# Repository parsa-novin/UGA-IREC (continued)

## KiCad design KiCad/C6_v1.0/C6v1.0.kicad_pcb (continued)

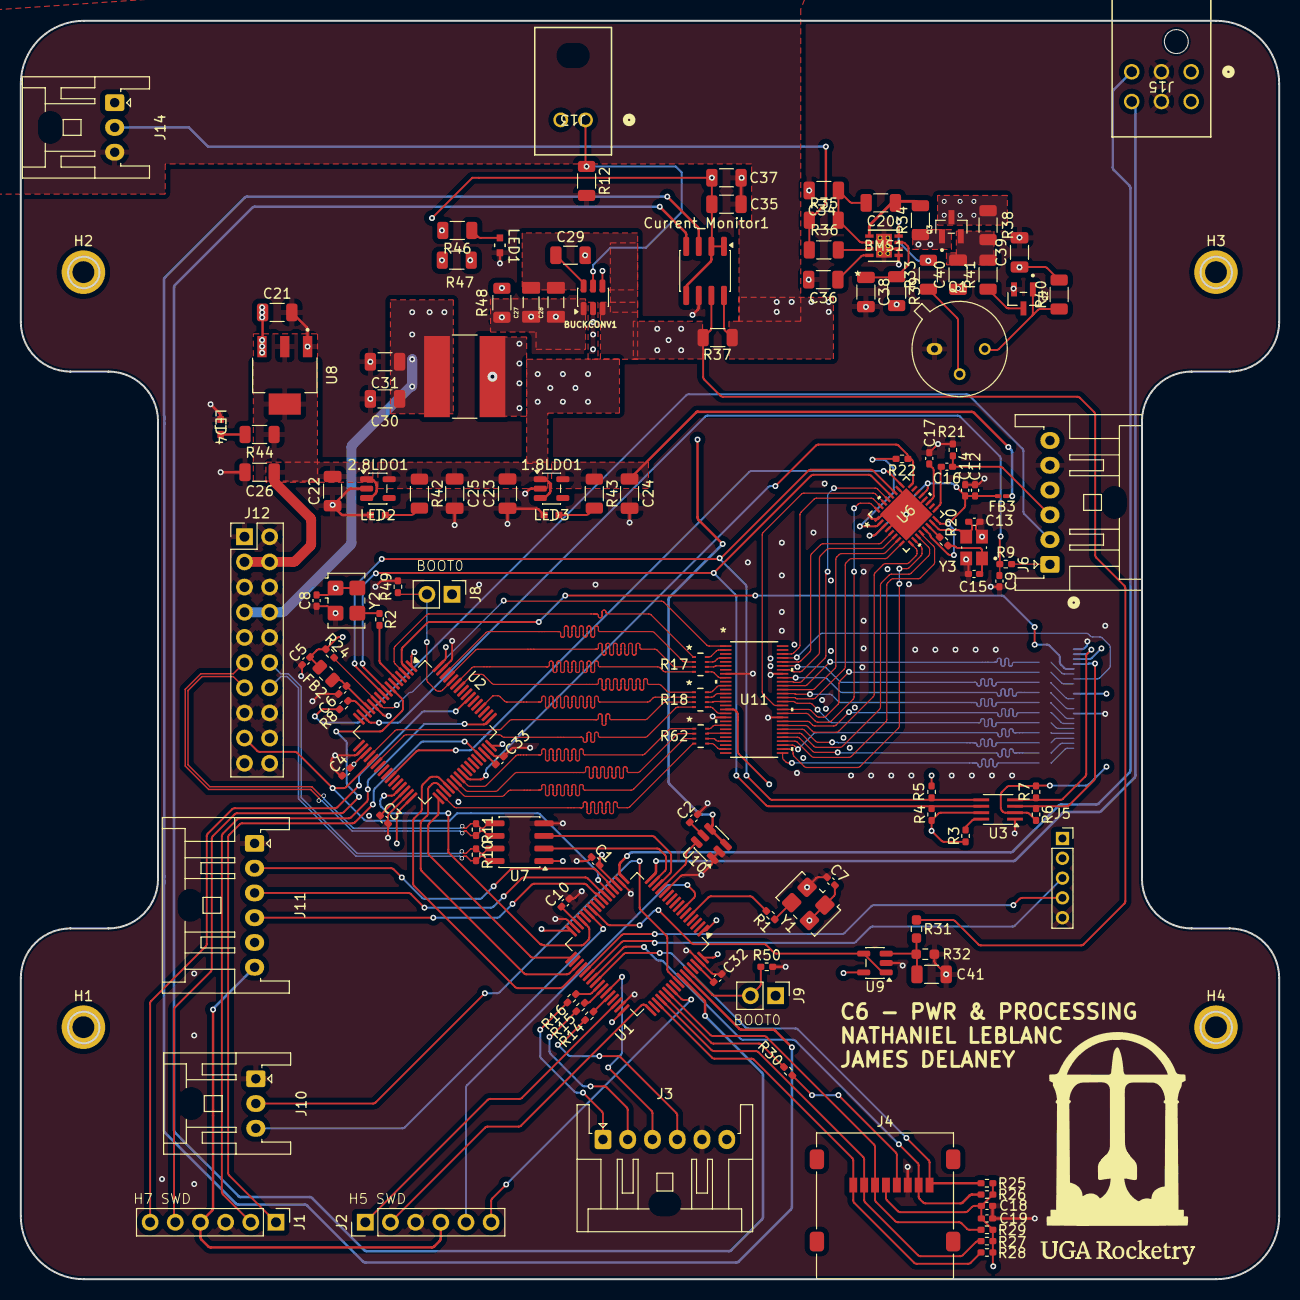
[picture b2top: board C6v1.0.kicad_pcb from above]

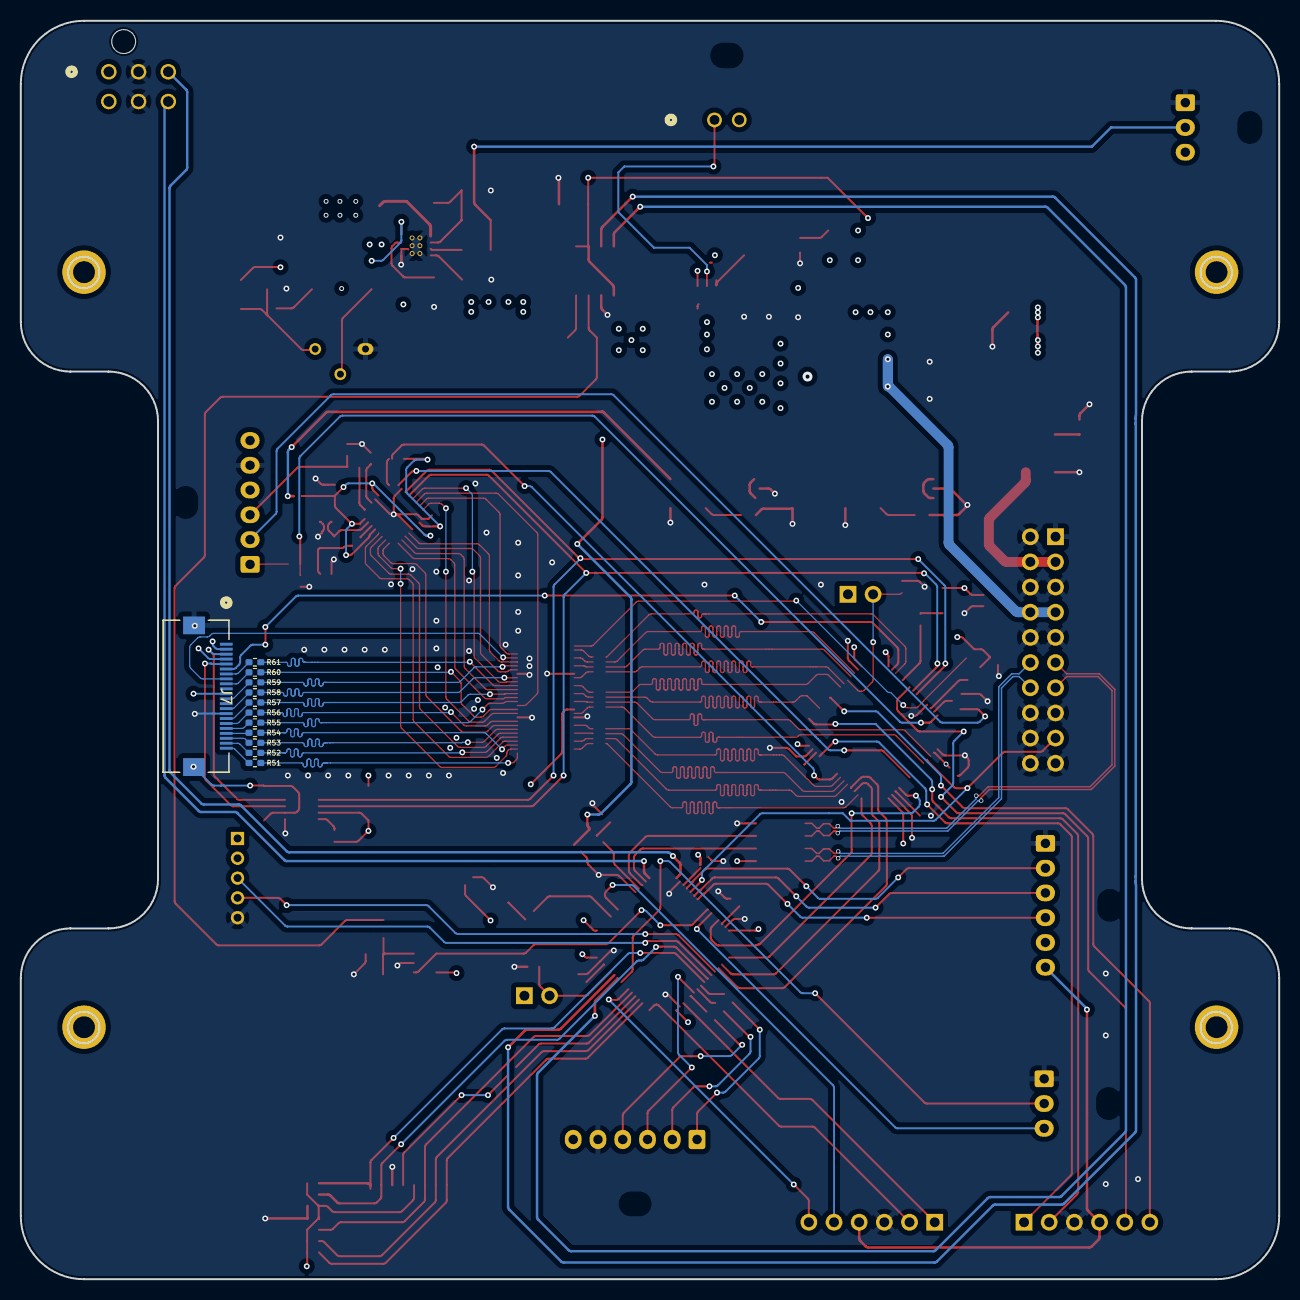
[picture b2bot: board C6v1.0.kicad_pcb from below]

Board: 4 copper layers, 127.0 x 127.0 mm, 144 parts (12 on the bottom side), 164 nets.

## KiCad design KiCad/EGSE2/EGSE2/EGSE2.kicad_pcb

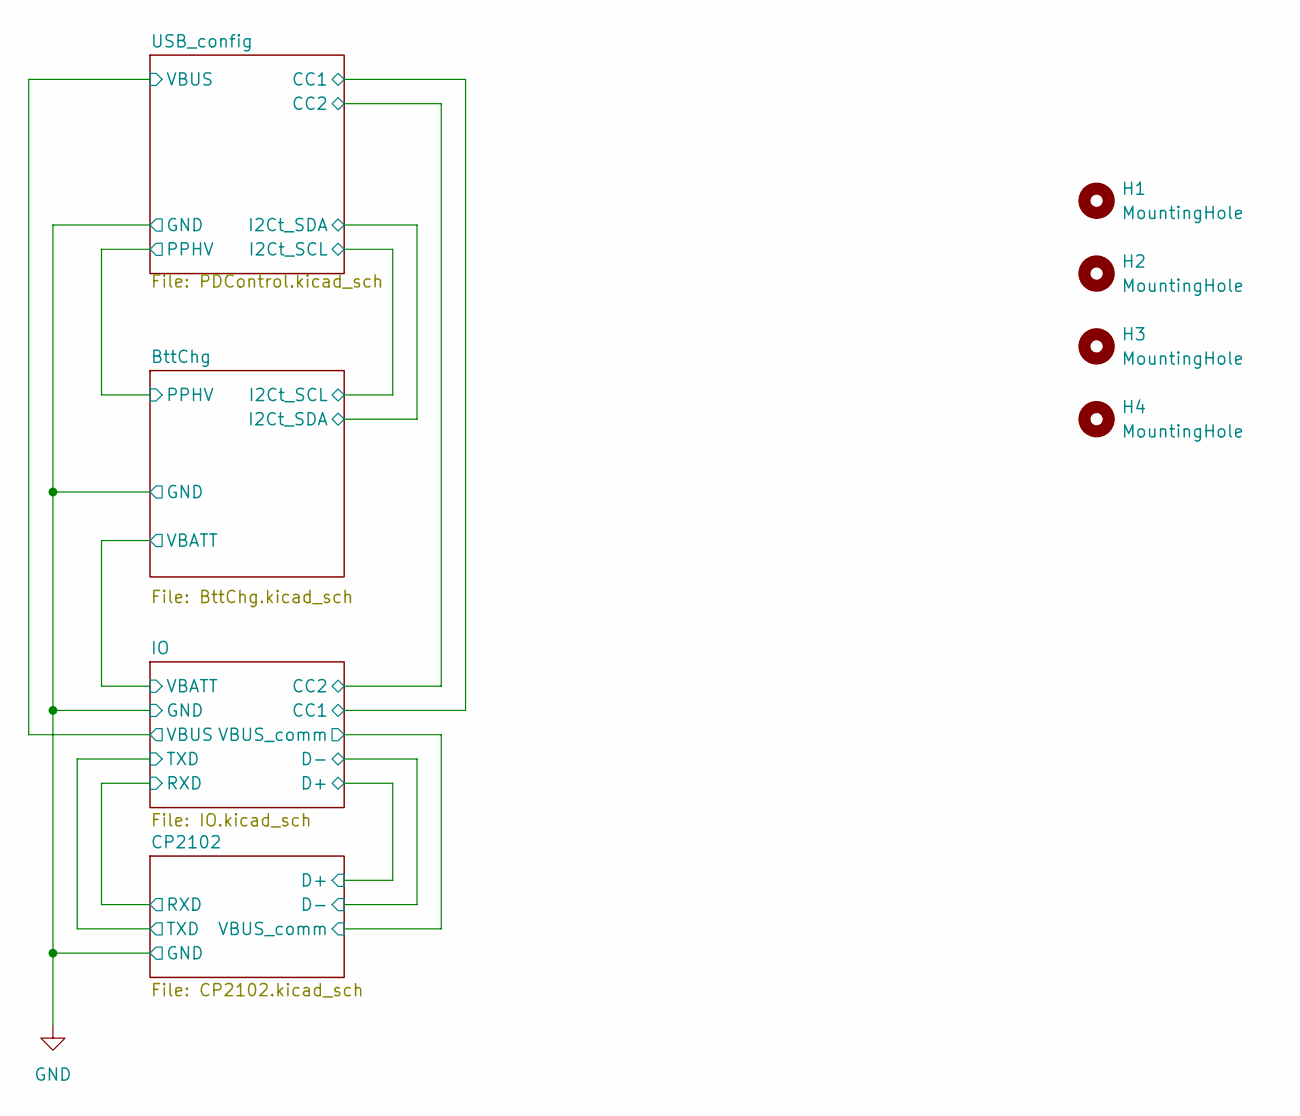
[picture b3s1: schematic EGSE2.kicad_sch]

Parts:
H1, H2, H3, H4: MountingHole; MountingHole_3mm_Pad

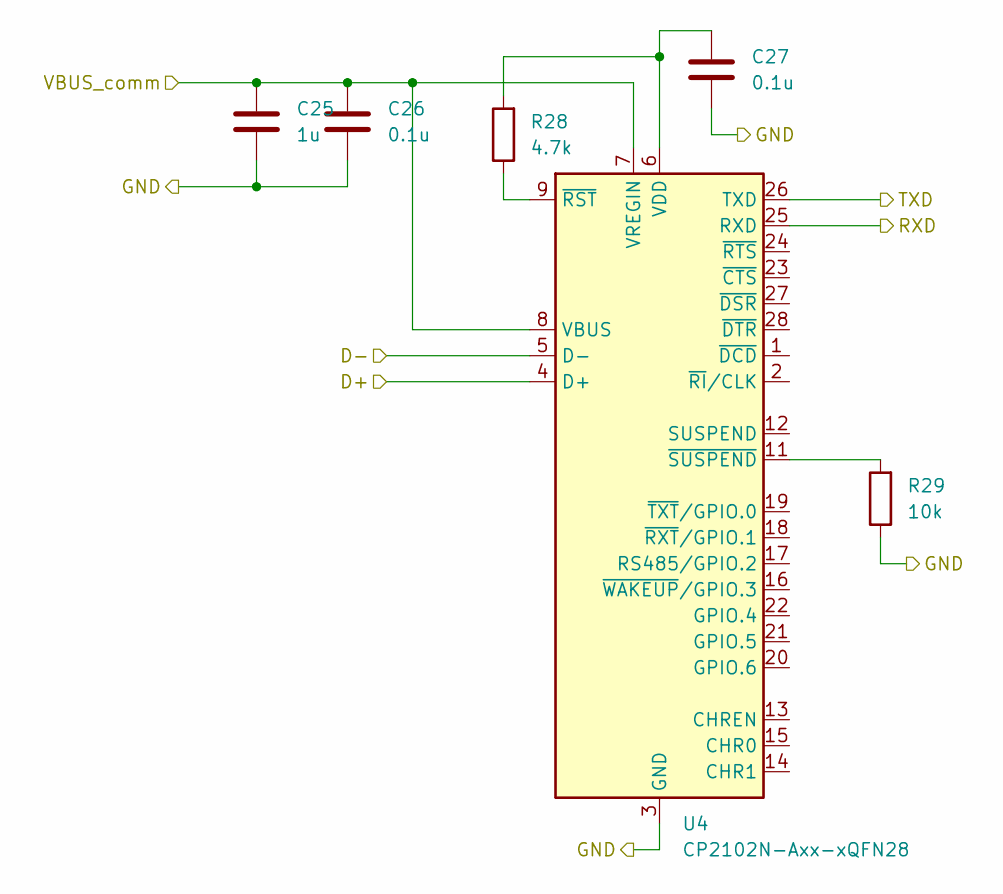
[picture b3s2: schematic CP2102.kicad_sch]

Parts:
C25: 1u; C_0805_2012Metric
C26, C27: 0.1u; C_0805_2012Metric
R28: 4.7k; R_0805_2012Metric_Pad1.20x1.40mm_HandSolder
R29: 10k; R_0805_2012Metric_Pad1.20x1.40mm_HandSolder
U4: CP2102N-Axx-xQFN28; QFN-28-1EP_5x5mm_P0.5mm_EP3.35x3.35mm

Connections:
/CP2102/D+: U4.4 (D+); also elsewhere on the board
/CP2102/D-: U4.5 (D-); also elsewhere on the board
/CP2102/RXD: U4.25 (RXD); also elsewhere on the board
/CP2102/TXD: U4.26 (TXD); also elsewhere on the board
/CP2102/VBUS_comm: C25.1, C26.2, U4.7 (VREGIN), U4.8 (VBUS); also elsewhere on the board
GND: C25.2, C26.1, C27.1, R29.1, U4.3 (GND), U4.29 (GND); also elsewhere on the board
unnamed: C27.2, R28.2, U4.6 (VDD)
unnamed: R28.1, U4.9 (~RST)
unnamed: R29.2, U4.11 (~SUSPEND)

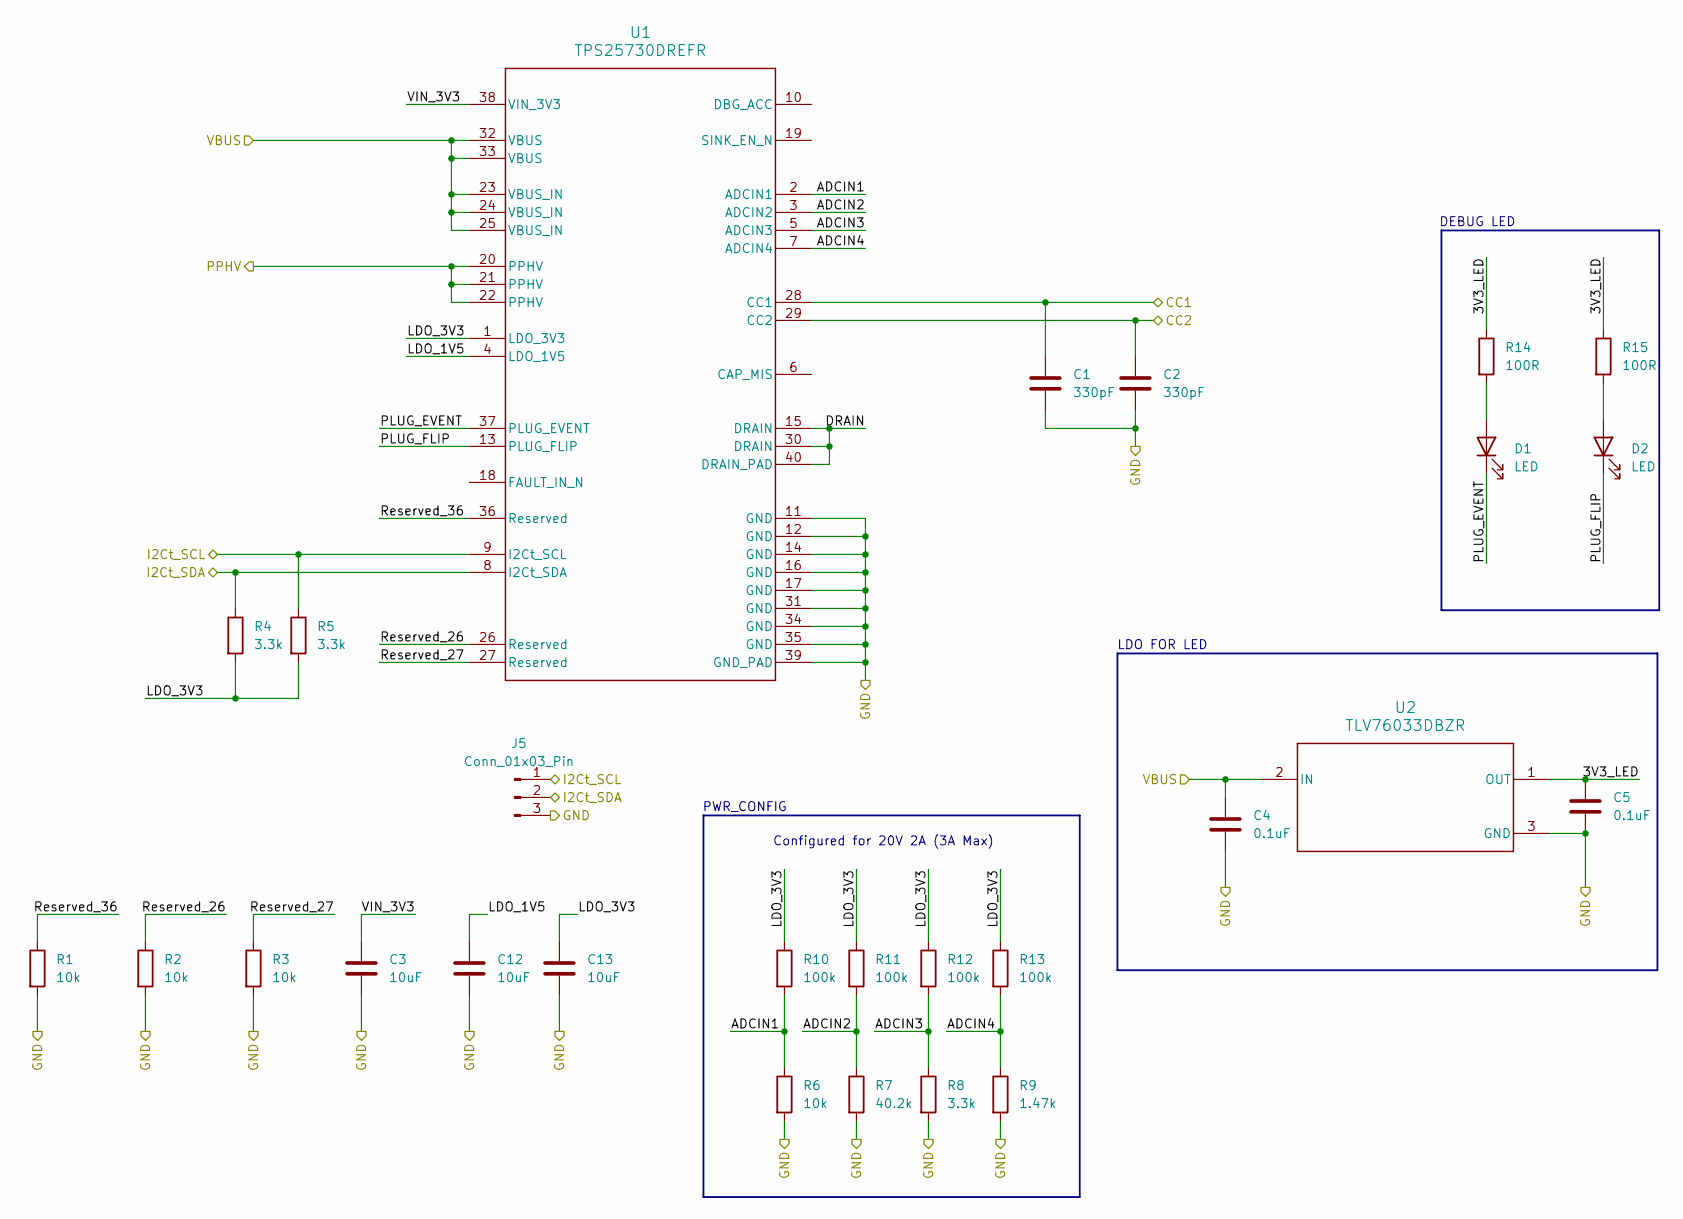
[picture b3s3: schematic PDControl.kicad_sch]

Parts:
C1, C2: 330pF; C_0805_2012Metric_Pad1.18x1.45mm_HandSolder
C3, C12, C13: 10uF; C_0805_2012Metric_Pad1.18x1.45mm_HandSolder
C4, C5: 0.1uF; C_0805_2012Metric_Pad1.18x1.45mm_HandSolder
D1, D2: LED; LED_0805_2012Metric_Pad1.15x1.40mm_HandSolder
J5: Conn_01x03_Pin; PinHeader_1x03_P2.54mm_Vertical
R1, R2, R3, R6: 10k; R_0805_2012Metric_Pad1.20x1.40mm_HandSolder
R4, R5, R8: 3.3k; R_0805_2012Metric_Pad1.20x1.40mm_HandSolder
R7: 40.2k; R_0805_2012Metric_Pad1.20x1.40mm_HandSolder
R9: 1.47k; R_0805_2012Metric_Pad1.20x1.40mm_HandSolder
R10, R11, R12, R13: 100k; R_0805_2012Metric_Pad1.20x1.40mm_HandSolder
R14, R15: 100R; R_0805_2012Metric_Pad1.20x1.40mm_HandSolder
U1: TPS25730DREFR; REF0038A-MFG
U2: TLV76033DBZR; DBZ0003A_N

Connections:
/BttChg/I2Ct_SCL: J5.1, R5.1, U1.9 (I2Ct_SCL); also elsewhere on the board
/BttChg/I2Ct_SDA: J5.2, R4.1, U1.8 (I2Ct_SDA); also elsewhere on the board
/BttChg/PPHV: U1.20 (PPHV), U1.21 (PPHV), U1.22 (PPHV); also elsewhere on the board
/IO/CC1: C1.1, U1.28 (CC1); also elsewhere on the board
/IO/CC2: C2.1, U1.29 (CC2); also elsewhere on the board
/IO/VBUS: C4.1, U1.23 (VBUS_IN), U1.24 (VBUS_IN), U1.25 (VBUS_IN), U1.32 (VBUS), U1.33 (VBUS), U2.2 (IN); also elsewhere on the board
/USB_config/3V3_LED: C5.1, R14.1, R15.1, U2.1 (OUT)
/USB_config/ADCIN1: R6.1, R10.2, U1.2 (ADCIN1)
/USB_config/ADCIN2: R7.1, R11.2, U1.3 (ADCIN2)
/USB_config/ADCIN3: R8.1, R12.2, U1.5 (ADCIN3)
/USB_config/ADCIN4: R9.1, R13.2, U1.7 (ADCIN4)
/USB_config/DRAIN: U1.15 (DRAIN), U1.30 (DRAIN), U1.40 (DRAIN_PAD)
/USB_config/LDO_1V5: C12.1, U1.4 (LDO_1V5)
/USB_config/LDO_3V3: C13.1, R4.2, R5.2, R10.1, R11.1, R12.1, R13.1, U1.1 (LDO_3V3)
/USB_config/PLUG_EVENT: D1.1 (K), U1.37 (PLUG_EVENT)
/USB_config/PLUG_FLIP: D2.1 (K), U1.13 (PLUG_FLIP)
/USB_config/Reserved_26: R2.1, U1.26 (Reserved)
/USB_config/Reserved_27: R3.1, U1.27 (Reserved)
/USB_config/Reserved_36: R1.1, U1.36 (Reserved)
/USB_config/VIN_3V3: C3.1, U1.38 (VIN_3V3)
GND: C1.2, C2.2, C3.2, C4.2, C5.2, C12.2, C13.2, J5.3, R1.2, R2.2, R3.2, R6.2, R7.2, R8.2, R9.2, U1.11 (GND), U1.12 (GND), U1.14 (GND), U1.16 (GND), U1.17 (GND), U1.31 (GND), U1.34 (GND), U1.35 (GND), U1.39 (GND_PAD), U2.3 (GND); also elsewhere on the board
unnamed: D1.2 (A), R14.2
unnamed: D2.2 (A), R15.2

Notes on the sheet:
LDO FOR LED
DEBUG LED
Configured for 20V 2A (3A Max)
PWR_CONFIG

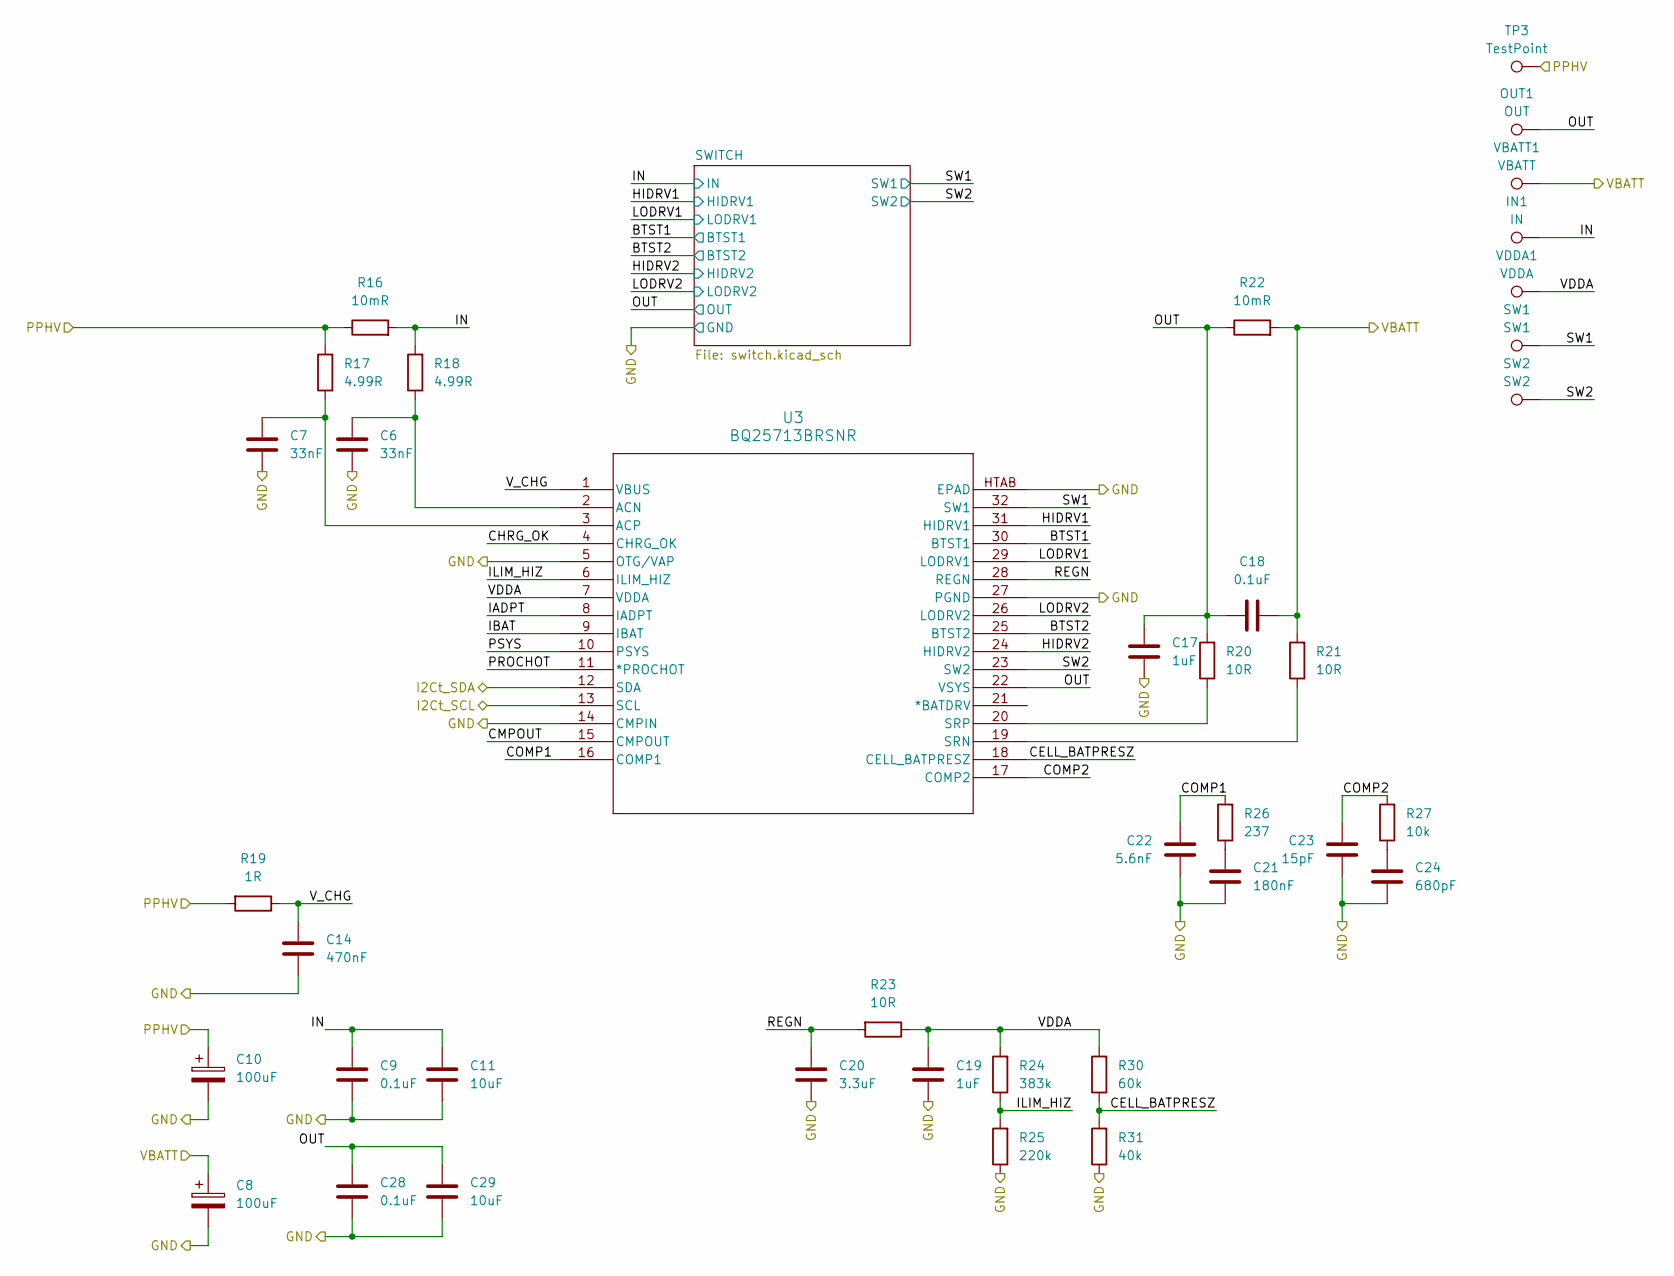
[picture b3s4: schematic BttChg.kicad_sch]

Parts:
C6, C7: 33nF; C_0805_2012Metric_Pad1.18x1.45mm_HandSolder
C8, C10: 100uF; CP_Elec_6.3x7.7
C9, C28: 0.1uF; C_0402_1005Metric_Pad0.74x0.62mm_HandSolder
C11, C29: 10uF; C_1206_3216Metric_Pad1.33x1.80mm_HandSolder
C14: 470nF; C_0805_2012Metric_Pad1.18x1.45mm_HandSolder
C17, C19: 1uF; C_0805_2012Metric_Pad1.18x1.45mm_HandSolder
C18: 0.1uF; C_0805_2012Metric_Pad1.18x1.45mm_HandSolder
C20: 3.3uF; C_0402_1005Metric_Pad0.74x0.62mm_HandSolder
C21: 180nF; C_0805_2012Metric_Pad1.18x1.45mm_HandSolder
C22: 5.6nF; C_0805_2012Metric_Pad1.18x1.45mm_HandSolder
C23: 15pF; C_0805_2012Metric_Pad1.18x1.45mm_HandSolder
C24: 680pF; C_0805_2012Metric_Pad1.18x1.45mm_HandSolder
IN1: IN; TestPoint_Pad_1.0x1.0mm
OUT1: OUT; TestPoint_Pad_1.0x1.0mm
R16, R22: 10mR; R_2512_6332Metric_Pad1.40x3.35mm_HandSolder
R17, R18: 4.99R; R_0805_2012Metric_Pad1.20x1.40mm_HandSolder
R19: 1R; R_0805_2012Metric_Pad1.20x1.40mm_HandSolder
R20, R21, R23: 10R; R_0805_2012Metric_Pad1.20x1.40mm_HandSolder
R24: 383k; R_0805_2012Metric_Pad1.20x1.40mm_HandSolder
R25: 220k; R_0805_2012Metric_Pad1.20x1.40mm_HandSolder
R26: 237; R_0805_2012Metric_Pad1.20x1.40mm_HandSolder
R27: 10k; R_0805_2012Metric_Pad1.20x1.40mm_HandSolder
R30: 60k; R_0805_2012Metric_Pad1.20x1.40mm_HandSolder
R31: 40k; R_0805_2012Metric_Pad1.20x1.40mm_HandSolder
SW1: SW1; TestPoint_Pad_1.0x1.0mm
SW2: SW2; TestPoint_Pad_1.0x1.0mm
TP3: TestPoint; TestPoint_Keystone_5019_Miniature
U3: BQ25713BRSNR; RSN32_TEX
VBATT1: VBATT; TestPoint_Pad_1.0x1.0mm
VDDA1: VDDA; TestPoint_Pad_1.0x1.0mm

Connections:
/BttChg/BTST1: U3.30 (BTST1); also elsewhere on the board
/BttChg/BTST2: U3.25 (BTST2); also elsewhere on the board
/BttChg/CELL_BATPRESZ: R30.1, R31.2, U3.18 (CELL_BATPRESZ)
/BttChg/CHRG_OK: U3.4 (CHRG_OK)
/BttChg/CMPOUT: U3.15 (CMPOUT)
/BttChg/COMP1: C22.1, R26.2, U3.16 (COMP1)
/BttChg/COMP2: C23.1, R27.2, U3.17 (COMP2)
/BttChg/HIDRV1: U3.31 (HIDRV1); also elsewhere on the board
/BttChg/HIDRV2: U3.24 (HIDRV2); also elsewhere on the board
/BttChg/I2Ct_SCL: U3.13 (SCL); also elsewhere on the board
/BttChg/I2Ct_SDA: U3.12 (SDA); also elsewhere on the board
/BttChg/IADPT: U3.8 (IADPT)
/BttChg/IBAT: U3.9 (IBAT)
/BttChg/ILIM_HIZ: R24.1, R25.2, U3.6 (ILIM_HIZ)
/BttChg/IN: C9.1, C11.1, IN1.1, R16.2, R18.2; also elsewhere on the board
/BttChg/LODRV1: U3.29 (LODRV1); also elsewhere on the board
/BttChg/LODRV2: U3.26 (LODRV2); also elsewhere on the board
/BttChg/OUT: C17.1, C18.1, C28.1, C29.1, OUT1.1, R20.2, R22.1, U3.22 (VSYS); also elsewhere on the board
/BttChg/PPHV: C10.1, R16.1, R17.2, R19.2, TP3.1; also elsewhere on the board
/BttChg/PROCHOT: U3.11 (*PROCHOT)
/BttChg/PSYS: U3.10 (PSYS)
/BttChg/REGN: C20.1, R23.2, U3.28 (REGN)
/BttChg/SW1: SW1.1, U3.32 (SW1); also elsewhere on the board
/BttChg/SW2: SW2.1, U3.23 (SW2); also elsewhere on the board
/BttChg/VBATT: C8.1, C18.2, R21.2, R22.2, VBATT1.1; also elsewhere on the board
/BttChg/VDDA: C19.1, R23.1, R24.2, R30.2, U3.7 (VDDA), VDDA1.1
/BttChg/V_CHG: C14.1, R19.1, U3.1 (VBUS)
GND: C6.2, C7.2, C8.2, C9.2, C10.2, C11.2, C14.2, C17.2, C19.2, C20.2, C21.2, C22.2, C23.2, C24.2, C28.2, C29.2, R25.1, R31.1, U3.5 (OTG/VAP), U3.14 (CMPIN), U3.27 (PGND), U3.HTAB (EPAD); also elsewhere on the board
unnamed: C21.1, R26.1
unnamed: C24.1, R27.1
unnamed: C6.1, R18.1, U3.2 (ACN)
unnamed: C7.1, R17.1, U3.3 (ACP)
unnamed: R21.1, U3.19 (SRN)
unnamed: R20.1, U3.20 (SRP)

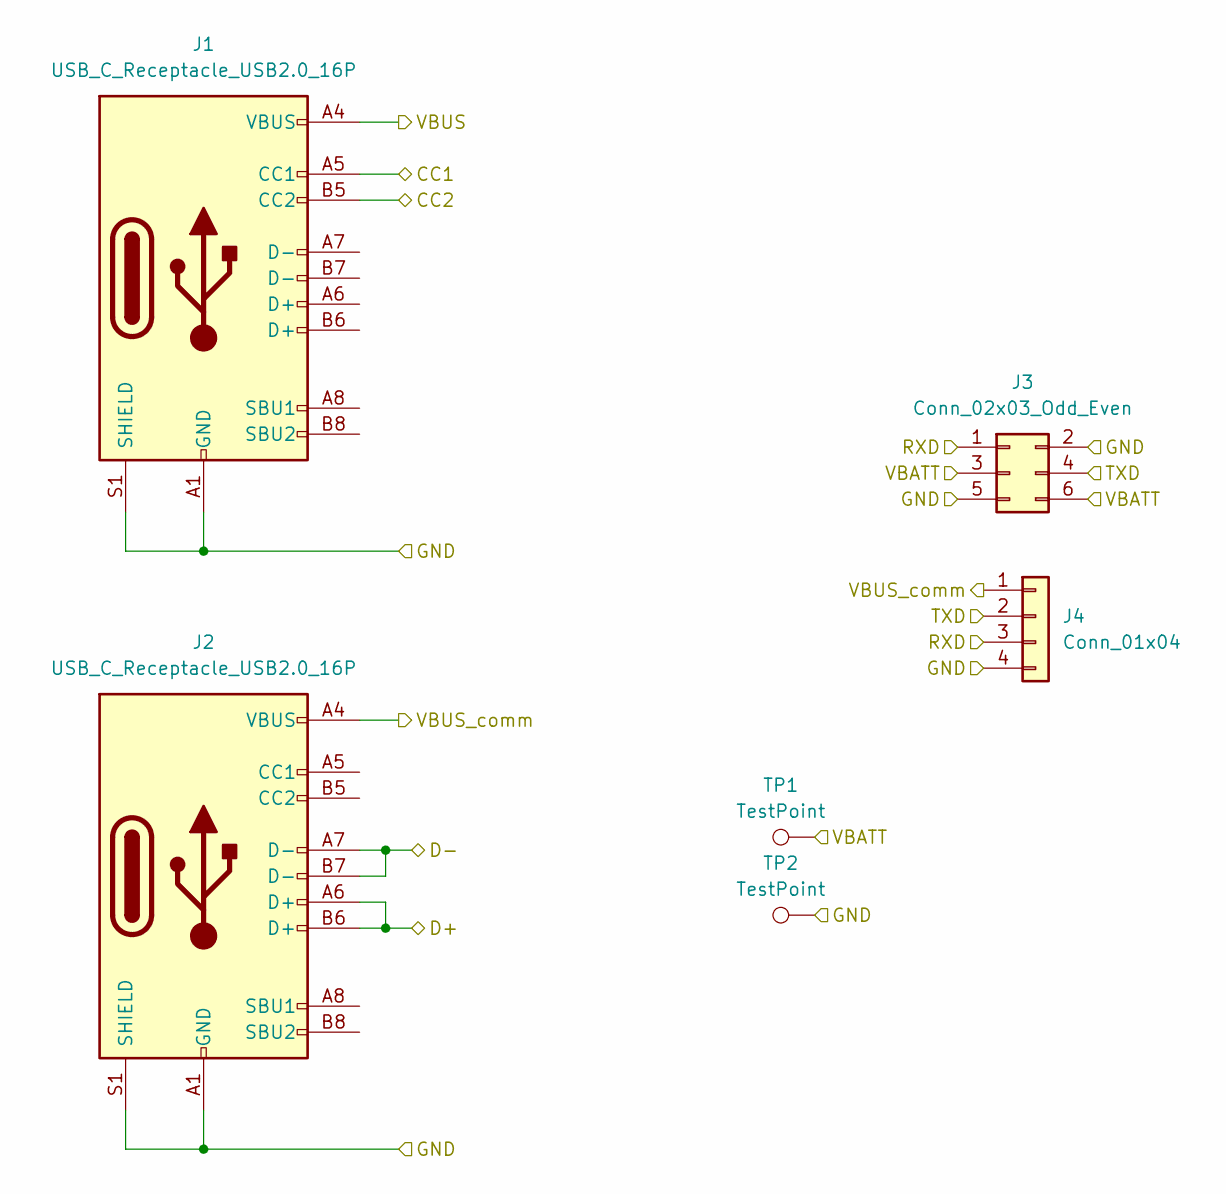
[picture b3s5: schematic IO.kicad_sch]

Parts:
J1, J2: USB_C_Receptacle_USB2.0_16P; USB_C_Receptacle_GCT_USB4085
J3: Conn_02x03_Odd_Even; CONN_SD-44764-001_06_MOL
J4: Conn_01x04; FanPinHeader_1x04_P2.54mm_Vertical
TP1, TP2: TestPoint; TestPoint_Keystone_5019_Miniature

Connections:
/BttChg/VBATT: J3.3, J3.6, TP1.1; also elsewhere on the board
/CP2102/D+: J2.A6 (D+), J2.B6 (D+); also elsewhere on the board
/CP2102/D-: J2.A7 (D-), J2.B7 (D-); also elsewhere on the board
/CP2102/RXD: J3.1, J4.3; also elsewhere on the board
/CP2102/TXD: J3.4, J4.2; also elsewhere on the board
/CP2102/VBUS_comm: J2.A4 (VBUS), J2.A9 (VBUS), J2.B4 (VBUS), J2.B9 (VBUS), J4.1; also elsewhere on the board
/IO/CC1: J1.A5 (CC1); also elsewhere on the board
/IO/CC2: J1.B5 (CC2); also elsewhere on the board
/IO/VBUS: J1.A4 (VBUS), J1.A9 (VBUS), J1.B4 (VBUS), J1.B9 (VBUS); also elsewhere on the board
GND: J1.A1 (GND), J1.A12 (GND), J1.B1 (GND), J1.B12 (GND), J1.S1 (SHIELD), J2.A1 (GND), J2.A12 (GND), J2.B1 (GND), J2.B12 (GND), J2.S1 (SHIELD), J3.2, J3.5, J4.4, TP2.1; also elsewhere on the board

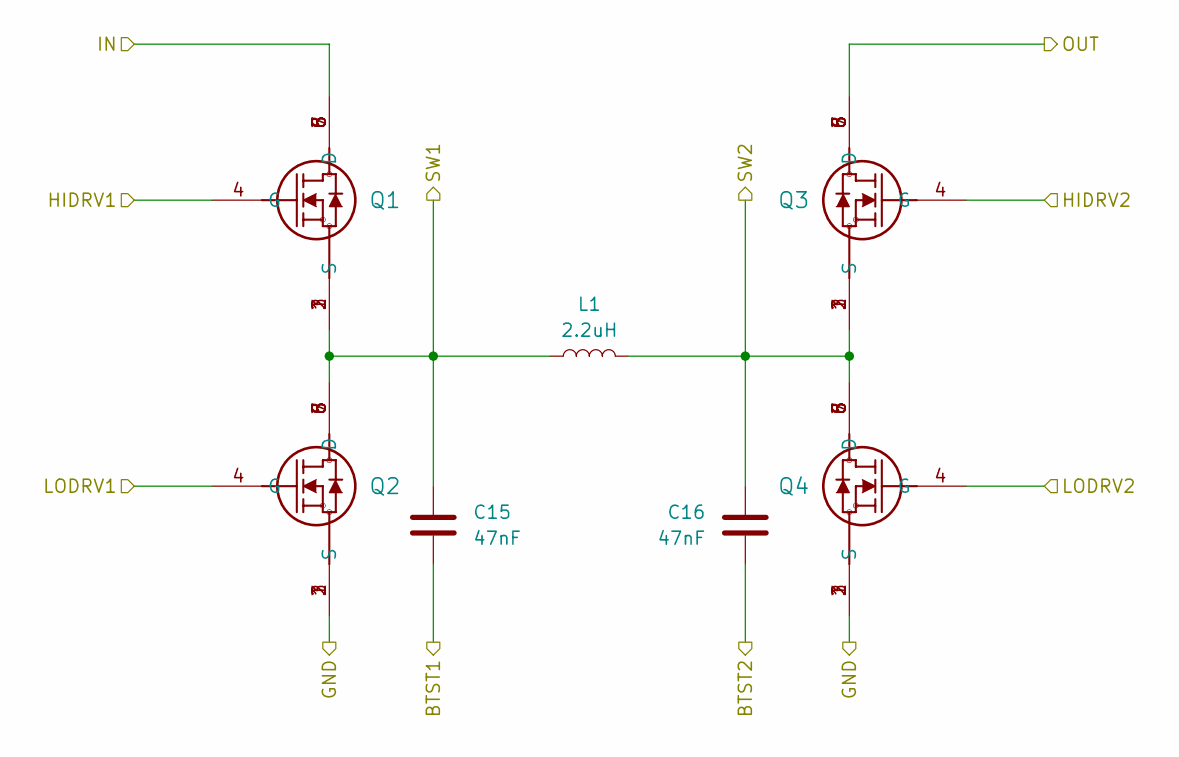
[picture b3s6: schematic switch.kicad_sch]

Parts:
C15, C16: 47nF; C_0805_2012Metric_Pad1.18x1.45mm_HandSolder
L1: 2.2uH; L_Bourns_SRN6045TA
Q1, Q2, Q3, Q4: SIS412DN-T1-GE3; POWERPAK_1212-8

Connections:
/BttChg/BTST1: C15.2; also elsewhere on the board
/BttChg/BTST2: C16.2; also elsewhere on the board
/BttChg/HIDRV1: Q1.4 (G); also elsewhere on the board
/BttChg/HIDRV2: Q3.4 (G); also elsewhere on the board
/BttChg/IN: Q1.5 (D), Q1.6 (D), Q1.7 (D), Q1.8 (D); also elsewhere on the board
/BttChg/LODRV1: Q2.4 (G); also elsewhere on the board
/BttChg/LODRV2: Q4.4 (G); also elsewhere on the board
/BttChg/OUT: Q3.5 (D), Q3.6 (D), Q3.7 (D), Q3.8 (D); also elsewhere on the board
/BttChg/SW1: C15.1, L1.1, Q1.1 (S), Q1.2 (S), Q1.3 (S), Q2.5 (D), Q2.6 (D), Q2.7 (D), Q2.8 (D); also elsewhere on the board
/BttChg/SW2: C16.1, L1.2, Q3.1 (S), Q3.2 (S), Q3.3 (S), Q4.5 (D), Q4.6 (D), Q4.7 (D), Q4.8 (D); also elsewhere on the board
GND: Q2.1 (S), Q2.2 (S), Q2.3 (S), Q4.1 (S), Q4.2 (S), Q4.3 (S); also elsewhere on the board

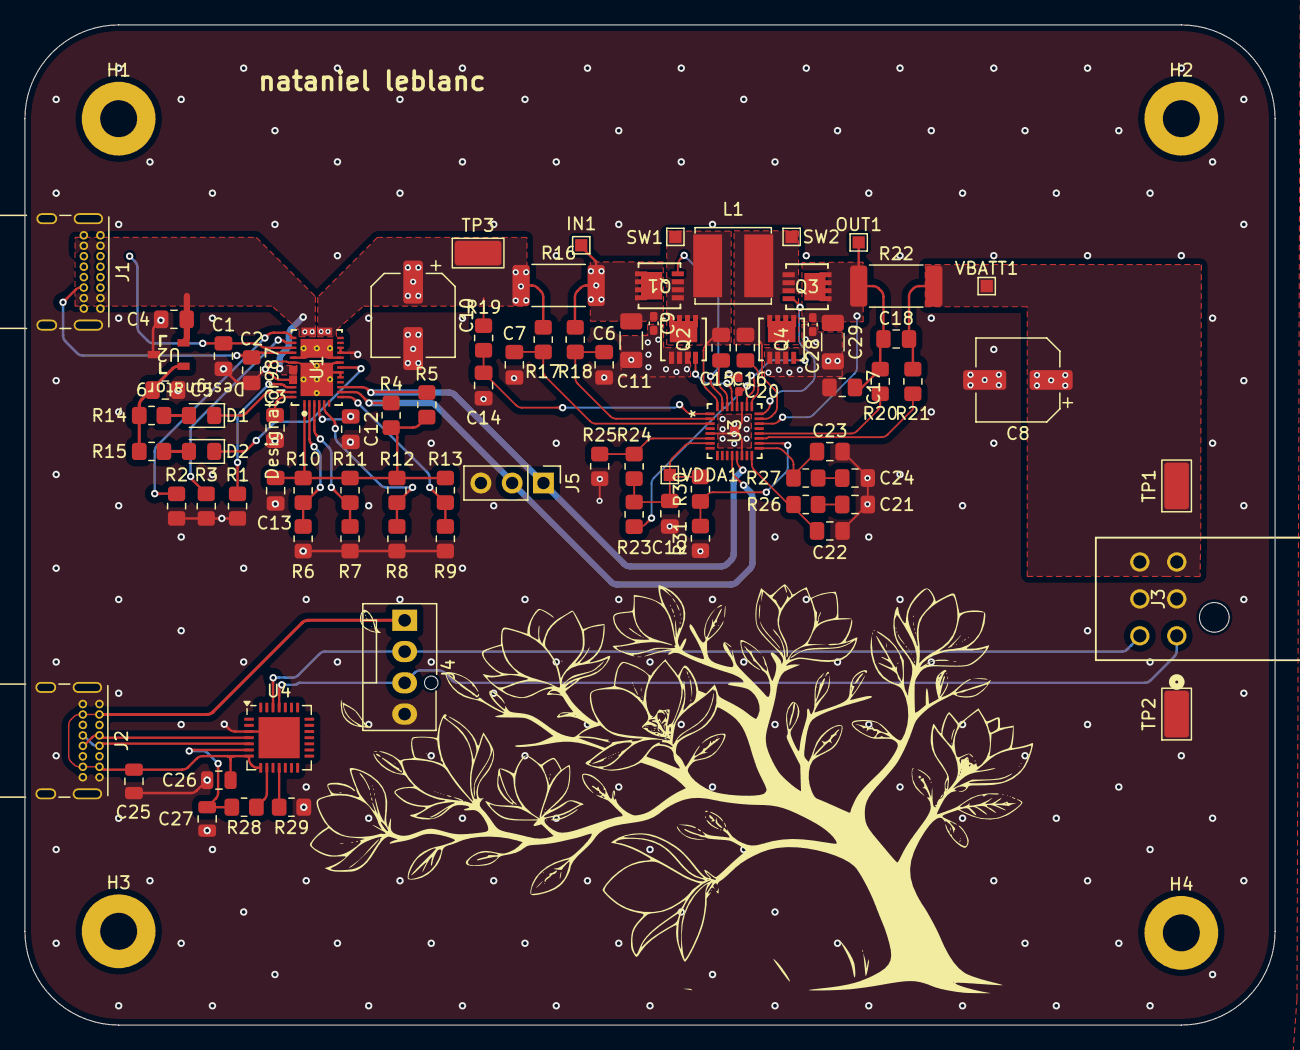
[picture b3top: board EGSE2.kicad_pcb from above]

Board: 4 copper layers, 101.6 x 81.3 mm, 89 parts (0 on the bottom side), 55 nets.

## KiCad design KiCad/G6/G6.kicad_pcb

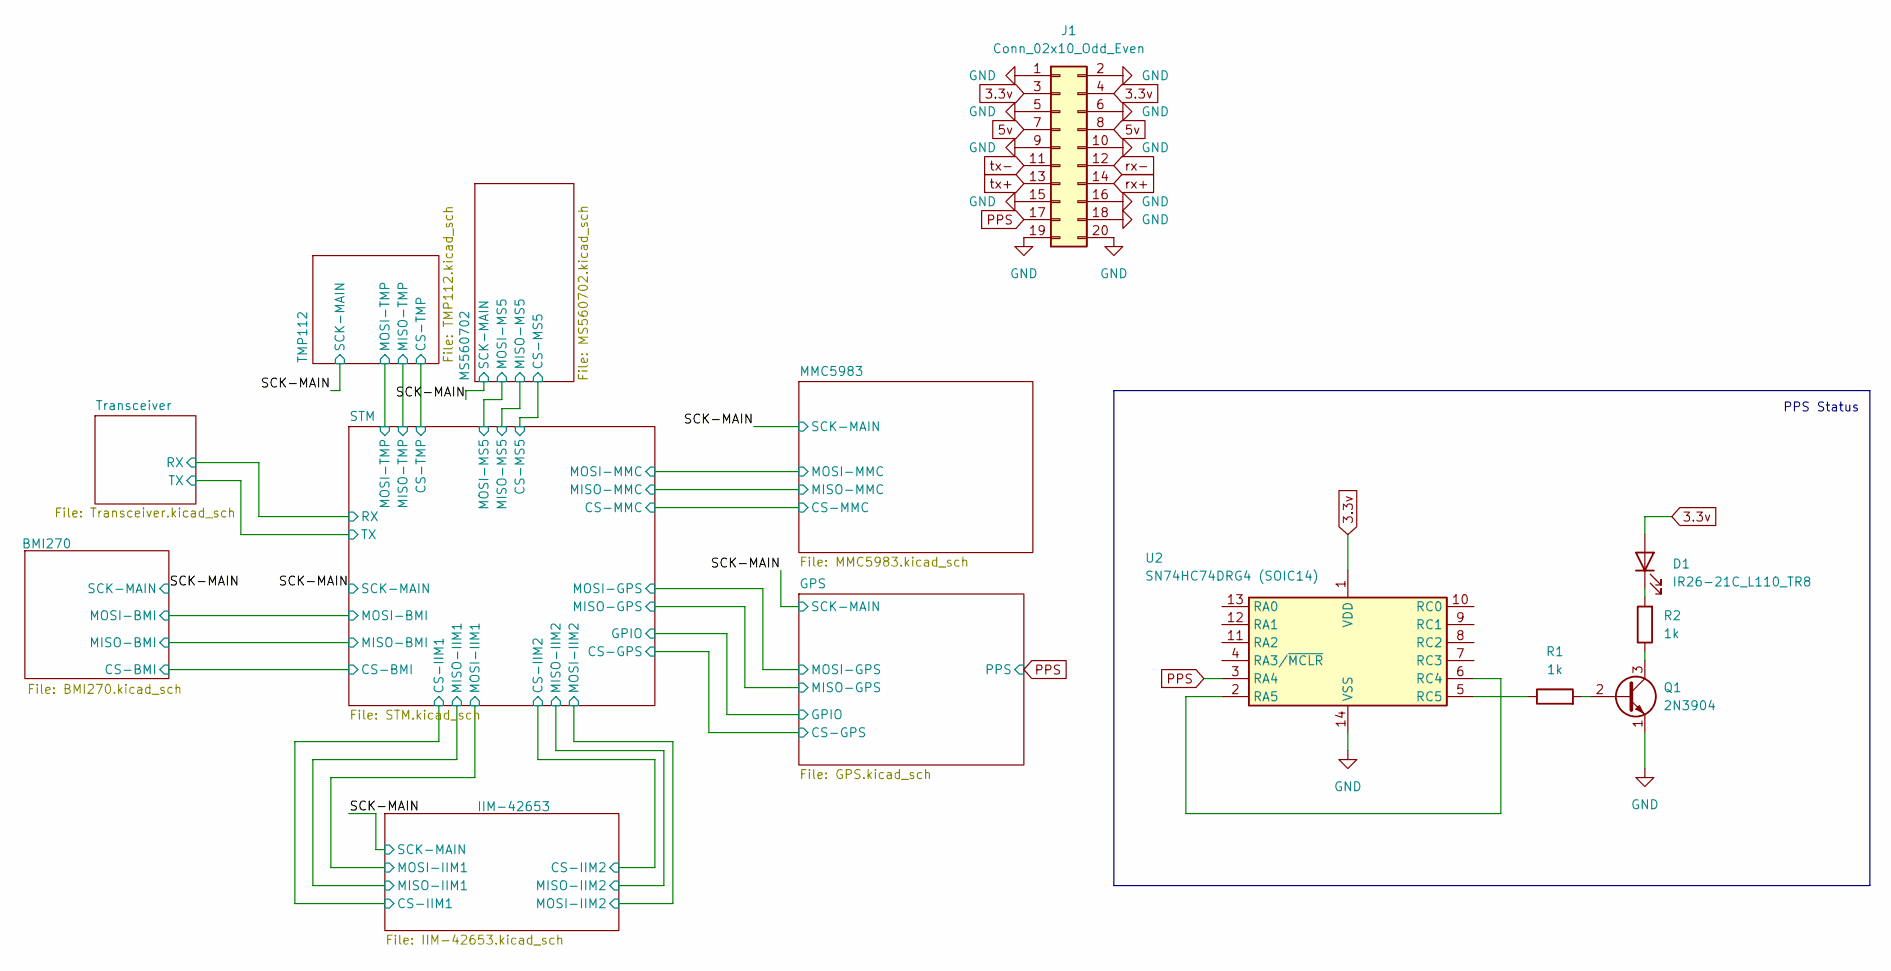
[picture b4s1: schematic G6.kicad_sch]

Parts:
D1: IR26-21C_L110_TR8; LED_1206_3216Metric
J1: Conn_02x10_Odd_Even; PinHeader_2x10_P2.54mm_Vertical
Q1: 2N3904; TO-92_Inline
R1, R2: 1k; R_1206_3216Metric
U2: SN74HC74DRG4 (SOIC14); SOIC-14_3.9x8.7mm_P1.27mm

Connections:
3.3v: D1.2 (A), J1.3, J1.4, U2.1 (VDD); also elsewhere on the board
5v: J1.7, J1.8
GND: J1.1, J1.2, J1.5, J1.6, J1.9, J1.10, J1.15, J1.16, J1.18, J1.19, J1.20, Q1.1 (E), U2.14 (VSS); also elsewhere on the board
unnamed: D1.1 (K), R2.2
unnamed: Q1.2 (B), R1.2
unnamed: Q1.3 (C), R2.1
unnamed: U2.2 (RA5), U2.6 (RC4)
unnamed: R1.1, U2.5 (RC5)
PPS: J1.17, U2.3 (RA4); also elsewhere on the board
rx+: J1.14; also elsewhere on the board
rx-: J1.12; also elsewhere on the board
tx+: J1.13; also elsewhere on the board
tx-: J1.11; also elsewhere on the board

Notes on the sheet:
PPS Status
